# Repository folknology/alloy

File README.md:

# Alloy
Alloy an OpenSource hardware fusion of FPGA and WiFi Microcontroller in a [Feather](https://learn.adafruit.com/adafruit-feather/feather-specification) compatible layout, a project of the myStorm communtiy.

Current status is hardware prototype, you can see the developments we are making on my regular streams :
*  [Live Stream, 8pm BST](https://www.twitch.tv/folknology)
* [Historic streams](https://www.youtube.com/watch?v=79OoLG_Dxk0&list=PLXS9jyX9czzodpJNL-szsMfl0rOrZk4B7)
Or at the join us at the [myStorm community forum](https://forum.mystorm.uk)

We will be using an Alloy fusion framework on top of [nMigen](https://github.com/m-labs/nmigen) and [Circuit Python](https://github.com/adafruit/circuitpython)

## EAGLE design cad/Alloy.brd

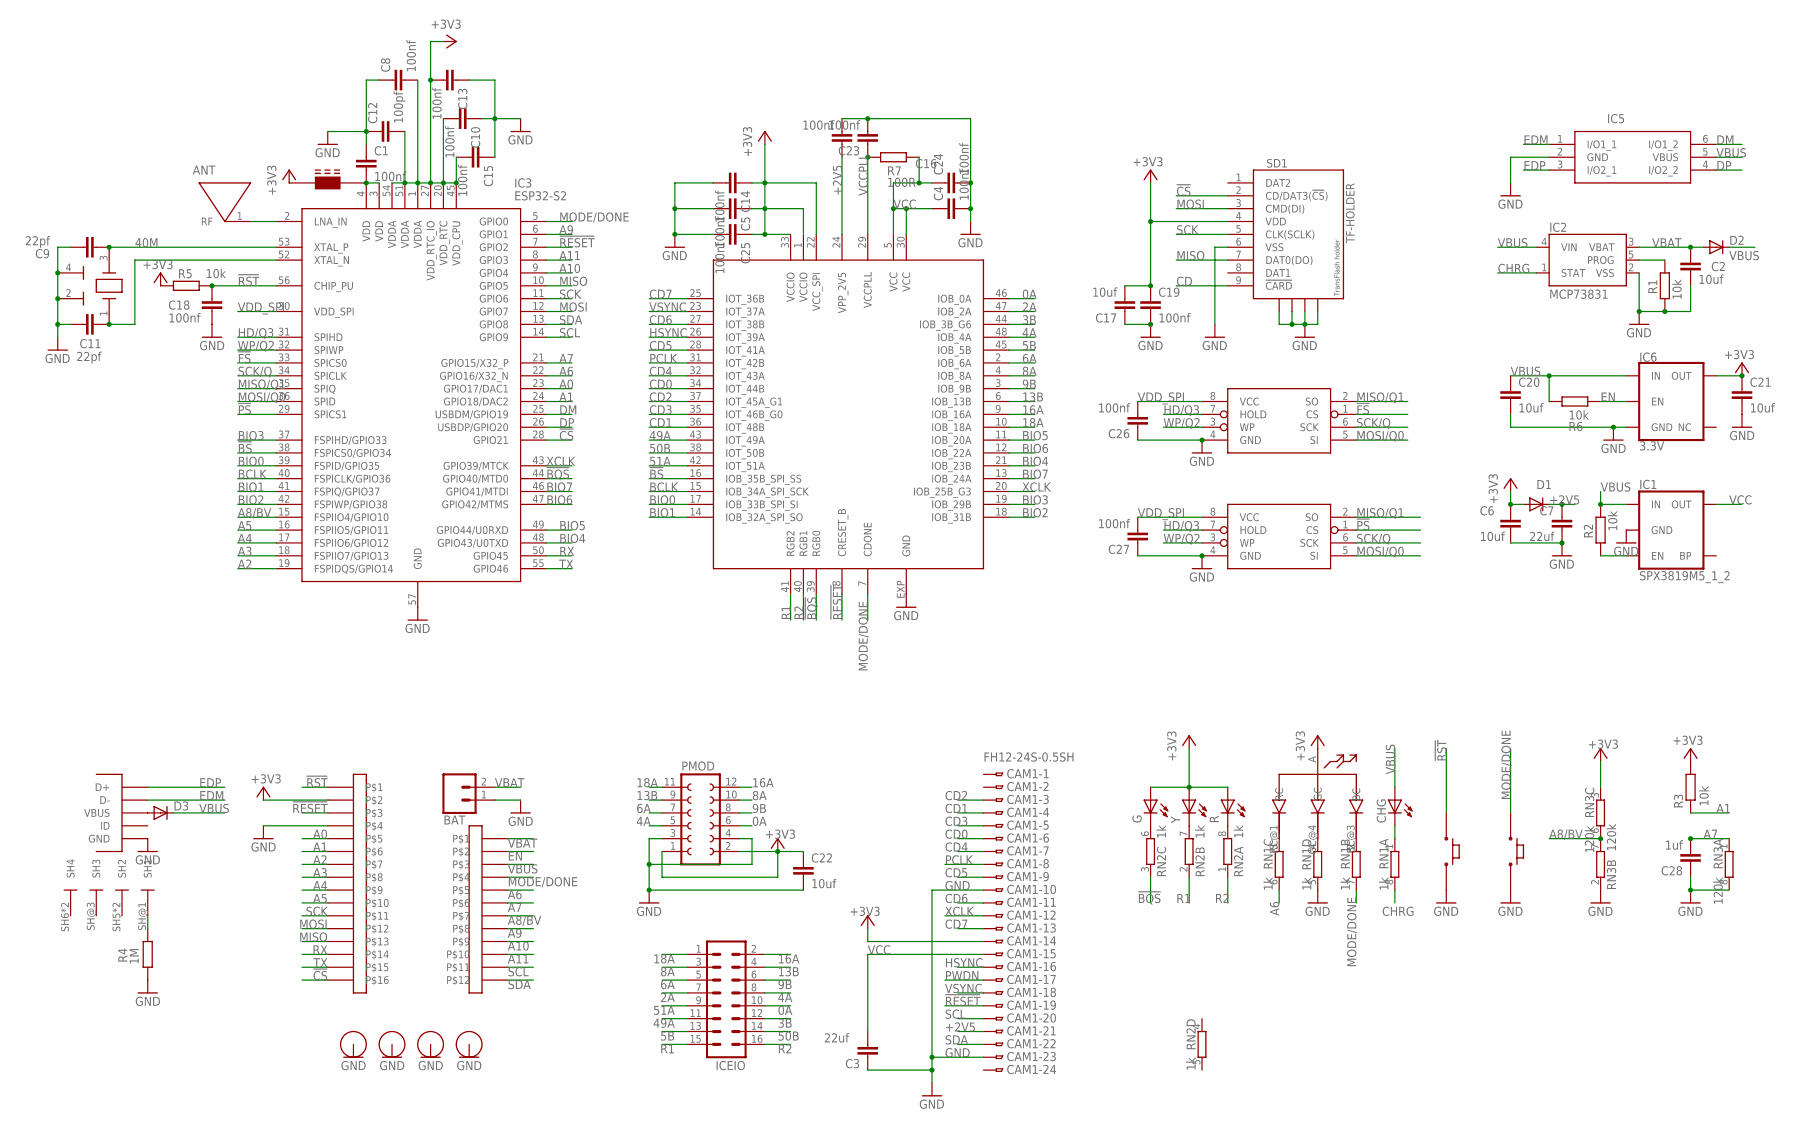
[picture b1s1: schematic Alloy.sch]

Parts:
ANT: 206513-0001; 2065130001
BAT: CONN_02-JST-2MM-SMT; JST-2-SMD
C1, C4, C5, C8, C10, C13, C14, C15, C16, C18, C19, C23, C24, C25, C26, C27: 100nf; C0402
C2, C6, C17, C20, C21, C22: 10uf; C0402
C3, C7: 22uf; C0603
C9, C11: 22pf; C0402
C12: 100pf; C0402
C28: 1uf; C0402
CAM1: FH12-24S-0.5SH
CHG: LEDCHIPLED_0603; CHIPLED_0603
D1: DIODE-SOD323-R; SOD323-R
D2, D3: DIODE-SOD123; SOD123
FB1: FERRITE_BEAD0402S; 0402S
FCL: 2.54-HEADER-16WTH-NS; 2.54_HEADER_16W_NS
FCU: 12X1X2.54-HEADERTH-NS; 2.54_HEADER_12W_NS
G: LEDCHIPLED_0603; CHIPLED_0603
H1, H2, H3, H4: HOLE2.5MM; 2.5MM-HOLE
IC1: SPX3819M5_1_2; SOT23-5
IC2: MCP73831; SOT23-5
IC3: ESP32-S2; QFN40P700X700X90-57N
IC4: ICE40UP5K; QFN48
IC5: USBLC6-2SC6; SOT95P280X145-6N
IC6: 3.3V; SOT23-5
IC7: LY68LXXXX; SO8
IC8: AT25SDF041A; SOIC-8-NARROW
ICEIO: MA08-2
PMOD: FE06-2W
R: LEDCHIPLED_0603; CHIPLED_0603
R1, R2, R3, R5, R6: 10k; R0402
R4: 1M; R0402
R7: 100R; R0402
RN1, RN2: 1k; 0603-ARV
RN3: 120k; 0603-ARV
SD1: TF-HOLDER; TF-PULL
U$1: RGB-PLCC-4; PLCC-4-SMALL
U$2: FCI-MICROUSB-B-PEG; MICROUSB-B-PEG
U$3, U$4: PUSH_BUTTON; 3X4MM_BUTTON
Y: LEDCHIPLED_0603; CHIPLED_0603
Y2: 12MZ; CRYSTAL-3.2X2.5

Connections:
0A: IC4.46 (IOB_0A), ICEIO.10, PMOD.6
2A: IC4.47 (IOB_2A), ICEIO.7
3B: IC4.44 (IOB_3B_G6), ICEIO.12
4A: IC4.48 (IOB_4A), ICEIO.8, PMOD.5
5B: IC4.45 (IOB_5B), ICEIO.13
6A: IC4.2 (IOB_6A), ICEIO.5, PMOD.7
8A: IC4.4 (IOB_8A), ICEIO.3, PMOD.10
9B: IC4.3 (IOB_9B), ICEIO.6, PMOD.8
13B: IC4.6 (IOB_13B), ICEIO.4, PMOD.9
16A: IC4.9 (IOB_16A), ICEIO.2, PMOD.12
18A: IC4.10 (IOB_18A), ICEIO.1, PMOD.11
40M: C9.2, IC3.53 (XTAL_P), Y2.3 (X2)
49A: IC4.43 (IOT_49A), ICEIO.11
50B: IC4.38 (IOT_50B), ICEIO.14
51A: IC4.42 (IOT_51A), ICEIO.9
!BQS: IC3.44 (GPIO40/MTD0), IC4.39 (RGB0), RN2.3 (1)
!BS: IC3.38 (FSPICS0/GPIO34), IC4.16 (IOB_35B_SPI_SS)
!CS: FCL.16, IC3.28 (GPIO21), SD1.2 (CD/DAT3(!CS!))
!FS: IC3.33 (SPICS0), IC8.1 (CS)
!PS: IC3.29 (SPICS1), IC7.1 (CS)
!RESET: CAM1.19, FCL.3, IC3.7 (GPIO2), IC4.8 (CRESET_B)
!RST: C18.1, FCL.1, IC3.56 (CHIP_PU), R5.1, U$3.P$1
+2V5: C7.2, C16.1, CAM1.21, D1.C, IC4.24 (VPP_2V5)
+3V3: C5.1, C6.1, C8.2, C10.2, C12.2, C13.2, C14.1, C15.2, C17.2, C19.1, C21.1, C22.1, C25.1, CAM1.14, D1.A, FB1.1, FCL.2, G.A, IC3.1 (VDDA), IC3.20 (VDD_RTC), IC3.27 (VDD_RTC_IO), IC3.45 (VDD_CPU), IC3.51 (VDDA), IC3.54 (VDDA), IC4.1 (VCCIO), IC4.22 (VCC_SPI), IC4.33 (VCCIO), IC6.5 (OUT), PMOD.1, PMOD.2, R.A, R3.1, R5.2, RN3.3 (1), SD1.4 (VDD), U$1.A (ANODE), Y.A
A0: FCL.5, IC3.23 (GPIO17/DAC1)
A1: FCL.6, IC3.24 (GPIO18/DAC2), R3.2
A2: FCL.7, IC3.19 (FSPIDQS/GPIO14)
A3: FCL.8, IC3.18 (FSPIIO7/GPIO13)
A4: FCL.9, IC3.17 (FSPIIO6/GPIO12)
A5: FCL.10, IC3.16 (FSPIIO5/GPIO11)
A6: FCU.5, IC3.22 (GPIO16/X32_N), RN1.6 (2)
A7: C28.2, FCU.6, IC3.21 (GPIO15/X32_P), RN3.1
A8/BV: FCU.7, IC3.15 (FSPIIO4/GPIO10), RN3.6 (2), RN3.7 (2)
A9: FCU.8, IC3.6 (GPIO1)
A10: FCU.9, IC3.9 (GPIO4)
A11: FCU.10, IC3.8 (GPIO3)
BCLK: IC3.40 (FSPICLK/GPIO36), IC4.15 (IOB_34A_SPI_SCK)
BIO0: IC3.39 (FSPID/GPIO35), IC4.17 (IOB_33B_SPI_SI)
BIO1: IC3.41 (FSPIQ/GPIO37), IC4.14 (IOB_32A_SPI_SO)
BIO2: IC3.42 (FSPIWP/GPIO38), IC4.18 (IOB_31B)
BIO3: IC3.37 (FSPIHD/GPIO33), IC4.19 (IOB_29B)
BIO4: IC3.48 (GPIO43/U0TXD), IC4.21 (IOB_23B)
BIO5: IC3.49 (GPIO44/U0RXD), IC4.11 (IOB_20A)
BIO6: IC3.47 (GPIO42/MTMS), IC4.12 (IOB_22A)
BIO7: IC3.46 (GPIO41/MTDI), IC4.13 (IOB_24A)
CD: SD1.9 (!CARD)
CD0: CAM1.6, IC4.34 (IOT_44B)
CD1: CAM1.4, IC4.36 (IOT_48B)
CD2: CAM1.3, IC4.37 (IOT_45A_G1)
CD3: CAM1.5, IC4.35 (IOT_46B_G0)
CD4: CAM1.7, IC4.32 (IOT_43A)
CD5: CAM1.9, IC4.28 (IOT_41A)
CD6: CAM1.11, IC4.27 (IOT_38B)
CD7: CAM1.13, IC4.25 (IOT_36B)
CHRG: IC2.1 (STAT), RN1.8 (2)
DM: IC3.25 (USBDM/GPIO19), IC5.6 (I/O1_2)
DP: IC3.26 (USBDP/GPIO20), IC5.4 (I/O2_2)
EDM: IC5.1 (I/O1_1), U$2.P$2 (D-)
EDP: IC5.3 (I/O2_1), U$2.P$3 (D+)
EN: FCU.2, IC6.3 (EN), R6.2
GND: BAT.1 (2), C1.1, C2.2, C3.1, C4.2, C5.2, C6.2, C7.1, C8.1, C9.1, C10.1, C11.1, C12.1, C13.1, C14.2, C15.1, C16.2, C17.1, C18.2, C19.2, C20.2, C21.2, C22.2, C23.2, C24.2, C25.2, C26.1, C27.1, C28.1, CAM1.10, CAM1.23, FCL.4, H1.P$1, H2.P$1, H3.P$1, H4.P$1, IC1.2 (GND), IC2.2 (VSS), IC3.57 (GND), IC4.EXP (GND), IC5.2 (GND), IC6.2 (GND), IC7.4 (GND), IC8.4 (GND), PMOD.3, PMOD.4, R1.2, R4.2, RN1.5 (2), RN3.2 (1), RN3.8 (2), SD1.6 (VSS), SD1.S1, SD1.S2, SD1.S3, SD1.S4, U$2.P$5 (GND), U$3.P$2, U$4.P$2, Y2.2 (GND), Y2.4 (GND)
HD/Q3: IC3.31 (SPIHD), IC7.7 (HOLD), IC8.7 (HOLD)
HSYNC: CAM1.16, IC4.26 (IOT_39A)
MISO: FCL.13, IC3.10 (GPIO5), SD1.7 (DAT0(DO))
MISO/Q1: IC3.35 (SPIQ), IC7.2 (SO), IC8.2 (SO)
MODE/DONE: FCU.4, IC3.5 (GPIO0), IC4.7 (CDONE), RN1.7 (2), U$4.P$1
MOSI: FCL.12, IC3.12 (GPIO7), SD1.3 (CMD(DI))
MOSI/Q0: IC3.36 (SPID), IC7.5 (SI), IC8.5 (SI)
unnamed: IC2.5 (PROG), R1.1
unnamed: ANT.1 (RF), IC3.2 (LNA_IN)
unnamed: IC1.3 (EN), R2.2
unnamed: R.C, RN2.8 (2)
unnamed: RN2.7 (2), Y.C
unnamed: C1.2, FB1.2, IC3.3 (VDD), IC3.4 (VDD)
unnamed: G.C, RN2.6 (2)
unnamed: R4.1, U$2.SH@1 (SH1)
unnamed: CHG.C, RN1.1
unnamed: D3.A, U$2.P$1 (VBUS)
unnamed: RN1.4 (1), U$1.GC@4 (GC)
unnamed: RN1.3 (1), U$1.RC@1 (RC)
unnamed: RN1.2 (1), U$1.BC@3 (BC)
unnamed: C11.2, IC3.52 (XTAL_N), Y2.1 (X1)
PCLK: CAM1.8, IC4.31 (IOT_42B)
PWDN: CAM1.17
R1: IC4.41 (RGB2), ICEIO.15, RN2.2 (1)
R2: IC4.40 (RGB1), ICEIO.16, RN2.1
RX: FCL.14, IC3.50 (GPIO45)
SCK: FCL.11, IC3.11 (GPIO6), SD1.5 (CLK(SCLK))
SCK/Q: IC3.34 (SPICLK), IC7.6 (SCK), IC8.6 (SCK)
SCL: CAM1.20, FCU.11, IC3.14 (GPIO9)
SDA: CAM1.22, FCU.12, IC3.13 (GPIO8)
TX: FCL.15, IC3.55 (GPIO46)
VBAT: BAT.2 (1), C2.1, D2.A, FCU.1, IC2.3 (VBAT)
VBUS: C20.1, CHG.A, D2.C, D3.C, FCU.3, IC1.1 (IN), IC2.4 (VIN), IC5.5 (VBUS), IC6.1 (IN), R2.1, R6.1
VCC: C3.2, C4.1, C24.1, CAM1.15, IC1.5 (OUT), IC4.5 (VCC), IC4.30 (VCC), R7.1
VCCPLL: C23.1, IC4.29 (VCCPLL), R7.2
VDD_SPI: C26.2, C27.2, IC3.30 (VDD_SPI), IC7.8 (VCC), IC8.8 (VCC)
VSYNC: CAM1.18, IC4.23 (IOT_37A)
WP/Q2: IC3.32 (SPIWP), IC7.3 (WP), IC8.3 (WP)
XCLK: CAM1.12, IC3.43 (GPIO39/MTCK), IC4.20 (IOB_25B_G3)

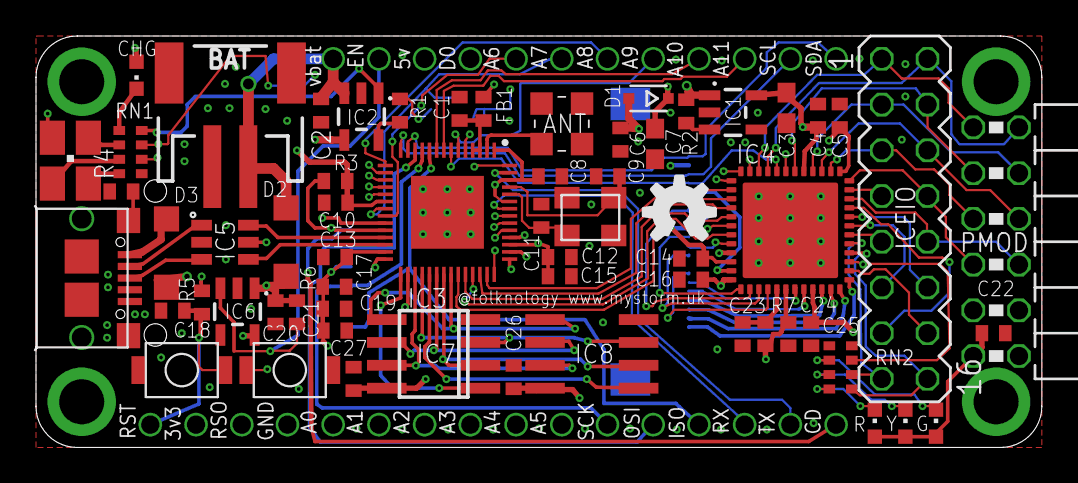
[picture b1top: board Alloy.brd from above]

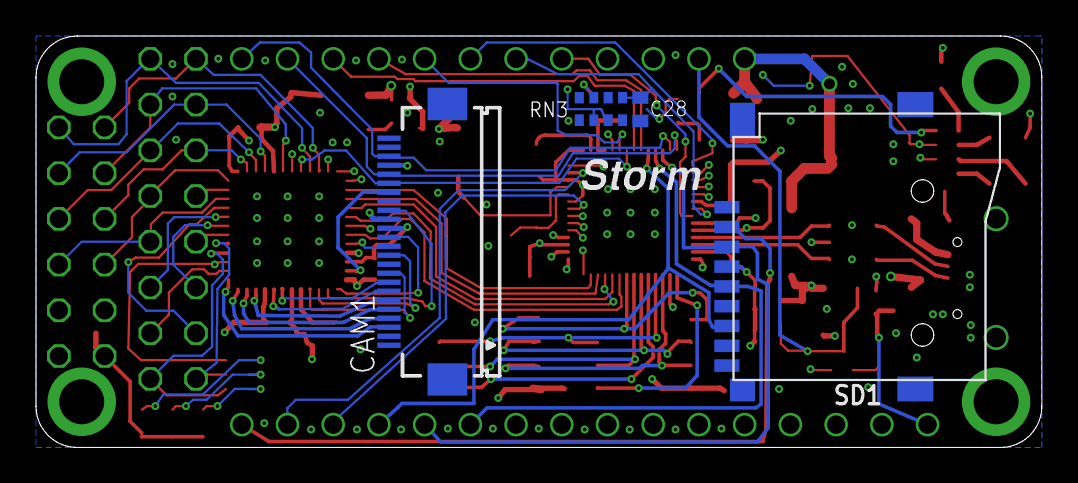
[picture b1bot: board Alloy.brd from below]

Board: 4 copper layers, 55.9 x 22.9 mm, 71 parts (4 on the bottom side), 98 nets.

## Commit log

2020-09-19 Added initial Cad schematic and PCB files
2020-09-19 Added the OS license to the repo
2020-09-19 Added Solderpad opensource hardware license
2020-09-19 Added Apache 2.0 license to cover all sub dirs without their own license file or wrapper
2020-09-19 Added Alloy layout image and referred to it in the Readmdded Allo layout image and referred to in the readme
2020-09-19 Corrected the Alloy image ref
2020-09-19 Added current state of project to the readme
2020-09-19 Minor corrections in the readme and myStorm community links added
2020-09-19 Added the schematic image
2020-09-19 Added feather links
2020-09-19 Updsated the readme and corrected some typos etc..
2020-09-19 Added a really basic CP example of programming the Ice40 from the ESP32-S2 which is bit banged DPI until I get scot's changes merged

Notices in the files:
parts and their libraries:
SparkFun-Connectors: Licensing: Creative Commons ShareAlike 4.0 International - https://creativecommons.org/licenses/by-sa/4.0
